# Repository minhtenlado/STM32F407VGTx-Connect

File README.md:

# STM32F407VGTx Connect — Wi-Fi & Bluetooth LE Development Board

**4-Layer PCB | KiCad 10 | STM32F407 + STM32F103 + ESP32-C3**

**Custom STM32 development board** based on the **STM32F407VGTx (ARM Cortex-M4)**, designed in **KiCad 10** with an **STM32F103CBTx onboard debug-probe circuit**, **USB Type-C**, **ESP32-C3 Wi-Fi/Bluetooth LE**, a **3.3 V / 3 A buck regulator**, and GPIO expansion headers.

> [!IMPORTANT]
> **Trạng thái dự án:** Repository chứa **schematic, PCB 4 lớp, hình ảnh 3D, Gerber/Drill, BOM, dữ liệu placement, thư viện AP63300WU-7 và mã nguồn firmware debug tham khảo**. Các file đã được thiết kế/xuất từ KiCad; **chưa có bằng chứng bo đã được lắp ráp và thử nghiệm thực tế**, cũng chưa có báo cáo ERC/DRC được xác minh kèm theo.
>
> **`firrmware_STLINKV2/` chứa mã nguồn [dap42](https://github.com/devanlai/dap42) (CMSIS-DAP nguồn mở), KHÔNG phải firmware ST-LINK/V2 chính hãng.** Không được mặc định rằng firmware tham khảo sẽ chạy ngay trên bo tự thiết kế nếu chưa kiểm tra chân MCU, USB và clock.

## 1. PCB 3D Preview

### Tổng quan bo mạch

### Hai góc nhìn 3D bổ sung

| 3D View 01 | 3D View 02|
| :---: | :---: |
|  |  |

> **Lưu ý:** Cả ba ảnh là bản dựng 3D từ KiCad, chưa phải ảnh bo mạch đã gia công hoặc lắp ráp. Nhấn vào từng ảnh để mở bản gốc.

## 2. PCB Layout — 4 Copper Layers

Bo mạch được thiết kế với **bốn lớp đồng**: `F.Cu`, `In1.Cu`, `In2.Cu`, `B.Cu`. Các hình dưới đây được lấy trực tiếp từ thư mục [`Images/`](Images/) trong project.

| Front Copper — `F.Cu` | Inner Copper 1 — `In1.Cu` |
| :---: | :---: |
|  |  |

| Inner Copper 2 — `In2.Cu` | Back Copper — `B.Cu` |
| :---: | :---: |
|  |  |

### Toàn bộ các lớp đồng

### Bố trí footprint

> [!NOTE]
> Ảnh các lớp và tập tin sản xuất là **kết quả xuất thiết kế**. Chúng chưa chứng minh các đường tín hiệu đã qua kiểm tra SI/EMC, ERC/DRC hoặc kiểm thử phần cứng.

## 3. System Architecture

```mermaid
flowchart TB
    HOST["PC / Laptop"] -->|"USB Type-C / J2"| USB["USB D+ / D- + Type-C CC"]
    USB --> F103["STM32F103CBTx / U1<br/>Onboard CMSIS-DAP candidate"]
    F103 -->|"SWDIO / SWCLK / NRST"| F407["STM32F407VGTx / U3<br/>Main MCU — Cortex-M4"]
    F103 <-->|"USART / Virtual COM planned"| F407
    F407 <-->|"UART2"| ESP["ESP32-C3-WROOM-02 / U4<br/>2.4 GHz Wi-Fi + Bluetooth LE"]
    F407 --- GPIO["GPIO expansion headers"]
    USB -->|"VBUS / D3"| PWR["AP63300WU-7 / U5<br/>3.3 V Buck regulator"]
    PWR --> F103
    PWR --> F407
    PWR --> ESP
    PROG["External SWD programmer"] -->|"J1 / program the STM32F103"| F103
    EXT["External UART programmer"] -->|"J13 / ESP32 UART0"| ESP
```

Đây là **kiến trúc phần cứng dự kiến**. Các chức năng CMSIS-DAP, Virtual COM và Wi-Fi/BLE chỉ hoạt động sau khi có firmware đúng và kiểm thử trên bo thực tế.

## 4. Hardware Overview

| Khối | Linh kiện / đầu nối thực tế | Vai trò |
| --- | --- | --- |
| Main MCU | **U3 — STM32F407VGTx** | MCU ARM Cortex-M4, chạy ứng dụng chính |
| Debug MCU | **U1 — STM32F103CBTx** | Phần cứng debug probe tích hợp, dự kiến dùng CMSIS-DAP |
| Wireless | **U4 — ESP32-C3-WROOM-02** | Wi-Fi 2.4 GHz, Bluetooth Low Energy (BLE) |
| USB | **J2 — USB-C 2.0 (16 chân)** | USB dữ liệu và cấp nguồn đầu vào |
| USB ESD | **U2 — USBLC6-2SC6** | Bảo vệ ESD cho USB D+/D− |
| Power converter | **U5 — AP63300WU-7**, **L1 — 4.7 µH** | Buck 5 V sang 3.3 V, IC có định mức đầu ra tới 3 A |
| Reverse-current blocking | **D3 — SS34** | Diode Schottky trên đường cấp nguồn USB |
| Clocks | **Y1, Y2 — 8 MHz** | HSE riêng cho STM32F103 và STM32F407 |
| GPIO expansion | **J3, J4, J5, J11, J12** | Các chân mở rộng thể hiện trong project |
| Debug-MCU programming | **J1 — 1×5 header** | Nạp/khôi phục STM32F103 bằng SWD ngoài |
| ESP32 programming | **J13 — 1×5 header** | Đầu nối UART0 của ESP32-C3 |
| UART jumpers | **JP1, JP2** | Cho phép ngắt/nối UART giữa STM32F407 và ESP32 |
| User controls | **S1, S2, S3, SW2** | Các nút nhấn và công tắc theo schematic |
| Custom library | **`library/AP63300WU-7/`** | Symbol, footprint và mô hình STEP của U5 |

### Nguồn hệ thống

Nguồn USB đi qua **D3 (SS34)**; **AP63300WU-7** tạo đường **3.3 V** cho các mạch trên bo. Thiết kế Buck có **L1 = 4.7 µH**, tụ bootstrap, cầu chia áp FB và các tụ lọc đầu vào/đầu ra.

> [!WARNING]
> **3 A là định mức đầu ra của IC Buck, không phải mức dòng mà mọi cổng USB-C máy tính cho phép lấy.** Dòng khả dụng phụ thuộc nguồn USB, điện trở CC, dây cáp, bảo vệ quá dòng và tải thực tế. Cần kiểm tra dòng đỉnh của ESP32-C3, nhiệt độ linh kiện và khả năng cấp nguồn trước khi khai thác toàn bộ tải.
>
> USBLC6-2SC6 bảo vệ **xung ESD**; nó **không thay thế** thiết bị giới hạn quá dòng liên tục trên VBUS.

### HSE và RTC

- **Y1 = 8 MHz:** nguồn HSE dự kiến cho STM32F103.
- **Y2 = 8 MHz:** HSE của STM32F407, nối với **PH0/OSC_IN** và **PH1/OSC_OUT**.
- Các tụ tải được thể hiện trong schematic; giá trị cuối cần đối chiếu datasheet của đúng mã thạch anh và ký sinh layout.
- Thiết kế không sử dụng thạch anh RTC/LSE ngoài 32.768 kHz.

## 5. STM32 Programming, Debugging & UART

### A. Onboard debug path

Đường debug được thiết kế như sau:

`PC → J2 USB-C → U1 STM32F103 → SWD → U3 STM32F407`

| Chức năng | STM32F103 (U1) | STM32F407 (U3) |
| --- | --- | --- |
| SWDIO | PB14 | PA13 |
| SWCLK | PB13 | PA14 |
| Target reset | PB0 | NRST |
| UART đến MCU chính | PA2 / USART2_TX | PD9 / USART3_RX |
| UART từ MCU chính | PA3 / USART2_RX | PD8 / USART3_TX |

**Chân U1, U3 và tên net cần được đối chiếu trong bản schematic đang phát hành** trước khi thay đổi firmware hoặc PCB. Các đường SWD/UART được thiết kế cho chức năng debug và Virtual COM, **không có nghĩa thiết bị đã được nhận là ST-LINK trên PC**.

### B. First-time programming of debug MCU

**J1 là header dùng để nạp chính U1 (STM32F103)** theo BOM của project. Khi STM32F103 mới chưa có firmware, cần **probe SWD bên ngoài** để nạp firmware probe lần đầu. Không nhầm J1 với cổng debug mặc định của STM32F407.

### C. ESP32-C3 UART

Sơ đồ dành hai đường UART giữa MCU chính và ESP32-C3, qua **JP1/JP2**:

| STM32F407 | ESP32-C3 | Hướng tín hiệu |
| --- | --- | --- |
| PD5 / USART2_TX | GPIO6 (RX do firmware cấu hình) | STM32 → ESP32 |
| PD6 / USART2_RX | GPIO7 (TX do firmware cấu hình) | ESP32 → STM32 |

Đóng JP1/JP2 để nối UART. Trên ESP32-C3, UART có thể gán qua GPIO Matrix; firmware phải cấu hình đúng chân, điện áp logic **3.3 V**, tốc độ baud và giao thức.

## 6. Debugger Firmware — dap42 / CMSIS-DAP

Mã nguồn đi kèm được lưu tại [`firrmware_STLINKV2/`](firrmware_STLINKV2/). **Tên thư mục được giữ đúng như trong project, kể cả cách viết `firrmware`.**

> [!IMPORTANT]
> Đây là mã nguồn **[dap42](https://github.com/devanlai/dap42)** cho CMSIS-DAP, **không phải firmware ST-LINK/V2 chính thức**. Dự án dap42 có nhiều cấu hình STM32F103 cho các bo khác nhau. Cần sửa/đối chiếu chân debug, USB RENUM, LED, HSE và UART với phần cứng của project này trước khi sử dụng.

### Nội dung firmware hiện có

| Đường dẫn | Nội dung |
| --- | --- |
| [`firrmware_STLINKV2/src/`](firrmware_STLINKV2/src/) | Mã nguồn CMSIS-DAP, USB và cấu hình MCU |
| [`firrmware_STLINKV2/src/targets.mk`](firrmware_STLINKV2/src/targets.mk) | Danh sách build target |
| [`firrmware_STLINKV2/Makefile`](firrmware_STLINKV2/Makefile) | Hệ thống build |
| [`firrmware_STLINKV2/openocd/`](firrmware_STLINKV2/openocd/) | Ví dụ cấu hình OpenOCD |
| [`firrmware_STLINKV2/FLASHING.md`](firrmware_STLINKV2/FLASHING.md) | Hướng dẫn nạp firmware từ upstream |
| [`firrmware_STLINKV2/LICENSE`](firrmware_STLINKV2/LICENSE) | Giấy phép nguồn firmware |

### Biên dịch firmware tham khảo (Ubuntu)

Bản RAR **chưa có mã nguồn trong `firrmware_STLINKV2/libopencm3/`**; cần bổ sung dependency trước khi build.

```bash
sudo apt update
sudo apt install git make gcc-arm-none-eabi binutils-arm-none-eabi

cd firrmware_STLINKV2
# Chỉ thực hiện nếu thư mục libopencm3 đang trống
 git clone https://github.com/libopencm3/libopencm3.git libopencm3

# Ví dụ build cho profile STM32F103 Blue Pill của dap42:
make DAP103-BLUEPILL.bin
```

> [!CAUTION]
> **Không nạp thẳng file `DAP103-BLUEPILL.bin` lên U1 của PCB này** trước khi đối chiếu `src/stm32f103/bluepill/target.c`, `config.h`, mạch điều khiển USB pull-up `RENUM` và UART. Đây mới là ví dụ về **cách build target có sẵn**, không phải firmware đã tùy biến và kiểm chứng cho bo STM32F407 Wi-Fi/BLE.

Tham khảo thêm: [dap42 upstream](https://github.com/devanlai/dap42) · [libopencm3](https://github.com/libopencm3/libopencm3) · [OpenOCD](https://openocd.org/).

## 7. ESP32-C3 Wi-Fi & Bluetooth LE

**ESP32-C3-WROOM-02 (U4)** cung cấp kết nối **Wi-Fi 2.4 GHz và Bluetooth Low Energy**. ESP32-C3 **không hỗ trợ Bluetooth Classic**.

- **J13 (`ESP32_UART0_PROG`)**: chân UART0 phục vụ nạp và kiểm tra module.
- **JP1/JP2**: cầu nối UART với STM32F407.
- Dữ liệu qua Wi-Fi/BLE cần firmware riêng cho ESP32-C3; **project RAR hiện không chứa firmware ứng dụng hoàn chỉnh cho U3 hoặc U4**.
- Khi bố trí anten ESP32-C3 phải tuân thủ vùng keep-out, không đổ đồng hoặc đặt kim loại vào khu vực cấm theo tài liệu module.

## 8. Project Structure

```text
STM32F407VGTx_wifi/
├── README.md
├── STM32F407VGTx_wifi.kicad_pro      # KiCad project
├── STM32F407VGTx_wifi.kicad_sch      # Full schematic
├── STM32F407VGTx_wifi.kicad_pcb      # 4-layer PCB
├── schematic.pdf                     # PDF schematic
├── Images/
│   ├── board_3D(1).png              # 3D top view
│   ├── board_3D(2).png              # 3D isometric view
│   ├── board_3D(3).png              # 3D supplementary view
│   ├── F_cu.png                     # Front copper
│   ├── in1.png                      # Inner copper layer 1
│   ├── in2.png                      # Inner copper layer 2
│   ├── B_cu.png                     # Back copper
│   ├── ALL_layers.png               # All layers overview
│   └── footprint.png                # Component placement
├── production/
│   ├── STM32F407VGTx_wifi.zip       # Gerber + drill files (4 layers)
│   ├── bom.csv                      # Bill of materials
│   ├── positions.csv                # Component positions
│   ├── designators.csv              # Designator list
│   └── netlist.ipc                  # IPC netlist
├── library/
│   └── AP63300WU-7/                 # Custom symbol, footprint and STEP
│       ├── AP63300WU-7.kicad_sym
│       ├── SOT95P280X100-6N.kicad_mod
│       └── AP63300WU-7.step
└── firrmware_STLINKV2/              # Upstream dap42 CMSIS-DAP source
    ├── src/
    ├── openocd/
    ├── drivers/
    ├── Makefile
    ├── FLASHING.md
    ├── LICENSE
    └── README.md
```

> `Images/` dùng **chữ I viết hoa**; tên `in1.png` và `in2.png` cũng viết thường như trong RAR. GitHub phân biệt chữ hoa/chữ thường trong đường dẫn.

### Quick Links

| Tài nguyên | Liên kết |
| --- | --- |
| KiCad PCB | [STM32F407VGTx_wifi.kicad_pcb](STM32F407VGTx_wifi.kicad_pcb) |
| KiCad schematic | [STM32F407VGTx_wifi.kicad_sch](STM32F407VGTx_wifi.kicad_sch) |
| Schematic PDF | [schematic.pdf](schematic.pdf) |
| Gerber + Drill ZIP | [production/STM32F407VGTx_wifi.zip](production/STM32F407VGTx_wifi.zip) |
| BOM | [production/bom.csv](production/bom.csv) |
| Placement | [production/positions.csv](production/positions.csv) |
| Full images | [Images/](Images/) |
| CMSIS-DAP firmware source | [firrmware_STLINKV2/](firrmware_STLINKV2/) |
| AP63300WU-7 library | [library/AP63300WU-7/](library/AP63300WU-7/) |

### Mở project trên KiCad 10

1. Tải/clone repository rồi giữ nguyên cấu trúc thư mục.
2. Mở file `STM32F407VGTx_wifi.kicad_pro` bằng **KiCad 10**.
3. Kiểm tra và khai báo thư viện tùy chỉnh **AP63300WU-7** nếu KiCad báo không tìm thấy symbol/footprint.
4. Mở Schematic Editor → **Inspect → Electrical Rules Checker (ERC)**.
5. Mở PCB Editor → **Inspect → Design Rules Checker (DRC)**, kiểm tra lại netlist và quy tắc sản xuất trước khi xuất Gerber mới.

## 9. Verification Checklist

- [x] Có project KiCad 10 và schematic đầy đủ.
- [x] Có PCB **4 lớp đồng** `F.Cu`, `In1.Cu`, `In2.Cu`, `B.Cu`.
- [x] Có ba ảnh 3D, bốn ảnh lớp đồng, ảnh tổng hợp và footprint.
- [x] Có tập tin Gerber, drill, BOM, component positions và IPC netlist.
- [x] Có thiết kế STM32F407VGTx, STM32F103CBTx, ESP32-C3 và nguồn AP63300WU-7.
- [x] Có IC USBLC6-2SC6 bảo vệ ESD ở đường USB.
- [x] Có mã nguồn dap42/CMSIS-DAP để tham khảo tích hợp debug.
- [ ] Chạy và lưu **báo cáo ERC/DRC** với số lỗi đã xử lý.
- [ ] Xác nhận footprint, pin số, 3D model, vị trí pad và BOM trùng linh kiện đặt mua.
- [ ] Kiểm tra USB Type-C/CC, `RENUM`, bảo vệ VBUS và dòng cấp nguồn từ USB thực tế.
- [ ] Xác nhận HSE 8 MHz, VCAP, boot/reset, SWD và UART trên nguyên mẫu.
- [ ] Hoàn thiện bản firmware CMSIS-DAP tương thích chân U1 và kiểm tra nạp/debug U3.
- [ ] Hoàn thiện firmware STM32F407 và ESP32-C3, thử Wi-Fi/BLE thực tế.
- [ ] Thử nghiệm PCB đã lắp ráp, kiểm tra nhiệt, ổn định nguồn và mức nhiễu.

## 10. Safety & Licensing

- Các chân MCU, SWD, UART và ESP32-C3 dùng mức logic **3.3 V**, không tùy tiện cấp tín hiệu 5 V vào chân không chịu được 5 V.
- Tải dòng lớn qua USB cần có giới hạn dòng phù hợp; **định mức Buck 3 A không bảo đảm nguồn USB cấp được 3 A**.
- Các file sản xuất là **tài liệu thiết kế** và chưa thay thế cho báo cáo kiểm định phần cứng.
- **Phần cứng:** Repository chưa có `LICENSE` riêng xác nhận việc cấp phép lại schematic, PCB hoặc ảnh thiết kế. Việc công khai trên GitHub không tự động tương đương open-source hardware.
- **Firmware:** Mã nguồn dap42 là dự án bên thứ ba; giữ nguyên các giấy phép và thông báo bản quyền trong [`firrmware_STLINKV2/LICENSE`](firrmware_STLINKV2/LICENSE) và các thành phần liên quan.

---

**Designed by Phan Huynh Van Do** · **Hardware Rev 1.0** · **2026**

*STM32F407 Wi-Fi & Bluetooth Development Board — integrated debug, wireless connectivity and flexible embedded development.*

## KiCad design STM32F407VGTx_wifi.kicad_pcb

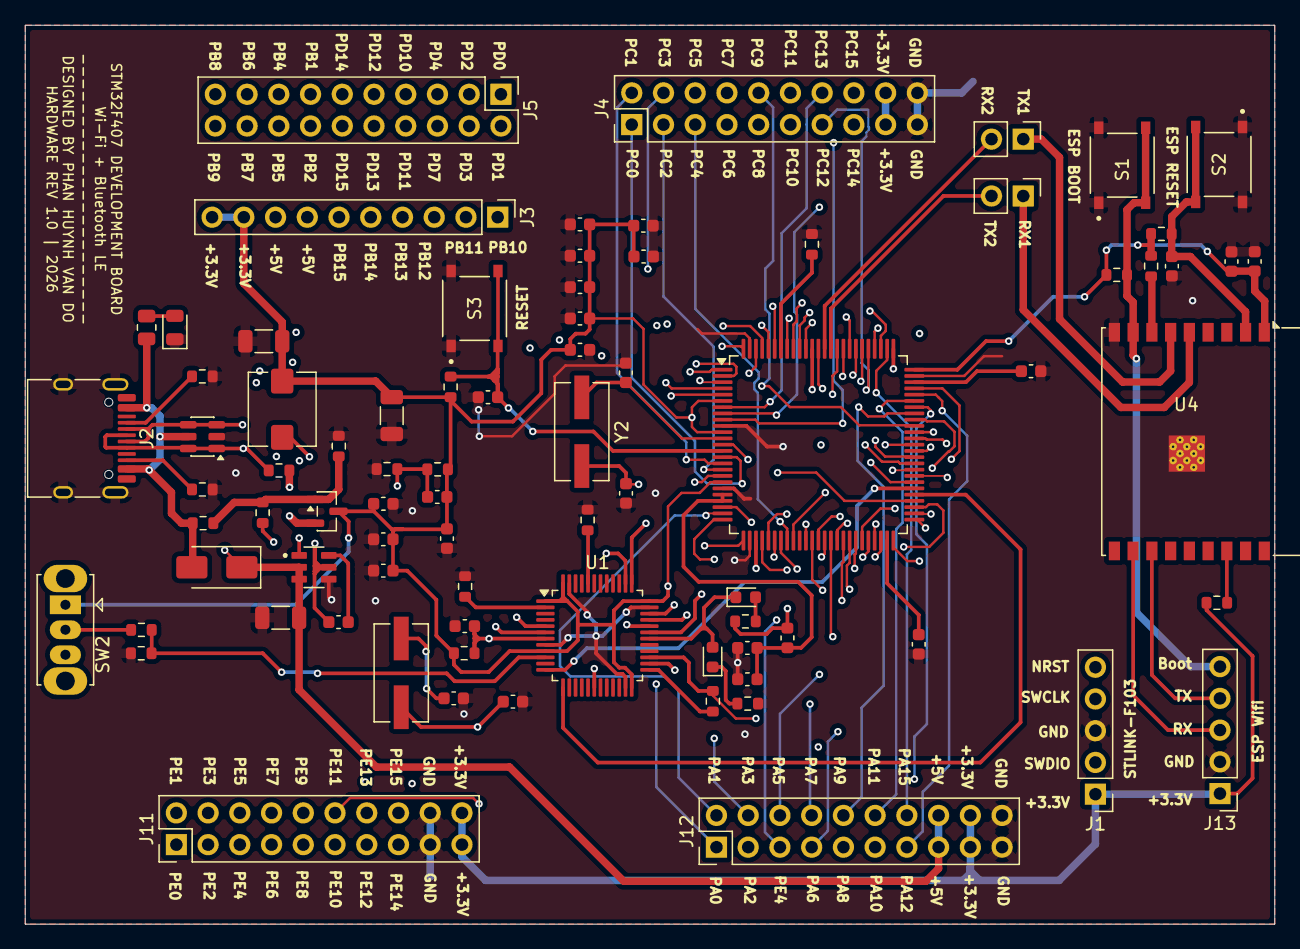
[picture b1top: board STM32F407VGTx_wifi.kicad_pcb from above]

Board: 4 copper layers, 100.0 x 71.9 mm, 81 parts (1 on the bottom side), 122 nets.

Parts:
C1, C4, C5, C6, C7, C12, C14, C15, C16, C17, C18, C19, C20, C21, C22, C25: 100nF; C_0603_1608Metric
C2, C3, C27, C28: 20pF; C_0603_1608Metric
C8: 10uF; C_1206_3216Metric
C9, C24: 22uF; C_1206_3216Metric
C10, C11: 2.2uF; C_0603_1608Metric
C13, C62: 1uF; C_0603_1608Metric
C23: 10uF; C_0603_1608Metric
C26: 56pF; C_0603_1608Metric
D1: RED; LED_0603_1608Metric
D2: BLUE; LED_0603_1608Metric
D3: SS34; D_SMA
D13: LED Red; LED_0805_2012Metric
FB1: FerriteBead; L_0603_1608Metric
J1: Dùng nạp cho U1; PinHeader_1x05_P2.54mm_Vertical
J2: USB_C_Receptacle_USB2.0_16P; USB_C_Receptacle_HRO_TYPE-C-31-M-12
J3: Conn_01x10_Pin; PinHeader_1x10_P2.54mm_Vertical
J4, J5: GPIO_B_C_D; PinHeader_2x10_P2.54mm_Vertical
J11: GPIO_D_E; PinHeader_2x10_P2.54mm_Vertical
J12: GPIO_A_B; PinHeader_2x10_P2.54mm_Vertical
J13: ESP32_UART0_PROG; PinHeader_1x05_P2.54mm_Vertical
JP1, JP2: Jumper_2_Open; PinHeader_1x02_P2.54mm_Vertical
L1: 4.7uH; L_Bourns_SRP5030T
Q1: BC849; SOT-23
R1, R2: 100k; R_0603_1608Metric
R3, R11, R14, R15, R18, R19, R20, R21: 10K; R_0603_1608Metric
R5, R7: 4K7; R_0603_1608Metric
R6, R10: 100R; R_0603_1608Metric
R8: 200R; R_0603_1608Metric
R9: 220R; R_0603_1608Metric
R12: 39K; R_0603_1608Metric
R13: 1K5; R_0603_1608Metric
R16, R17: 5.1K; R_0603_1608Metric
R22: 93.1K; R_0603_1608Metric
R23: 30.1K; R_0603_1608Metric
R58: 1K; R_0805_2012Metric
S1, S2, S3: TS-1187A-B-A-B; SW_TS-1187A-B-A-B
SW2: F103_USER_SW_3V3_GND; SW_Slide_SPDT_Straight_CK_OS102011MS2Q
U1: STM32F103CBTx; LQFP-48_7x7mm_P0.5mm
U2: USBLC6-2SC6; SOT-23-6
U3: STM32F407VGTx; LQFP-100_14x14mm_P0.5mm
U4: ESP32-C3-WROOM-02
U5: AP63300WU-7; SOT95P280X100-6N
WE: https://phanhuynh.id.vn/; //phanhuynh.id.vn/
Y1, Y2: 8MHz; Crystal_SMD_ECS_CSM3X-2Pin_7.6x4.1mm

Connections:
/+3V3_STLINK: C4.2, C5.2, C6.2, C7.2, C9.2, C15.2, C16.2, C17.2, C18.2, C19.2, C20.2, C21.2, C22.1, C23.1, C24.2, C26.2, FB1.1, J1.1, J3.9, J3.10, J4.17, J4.18, J11.19, J11.20, J12.17, J12.18, J13.1, L1.2, Q1.3 (C), R1.2, R8.1, R15.2, R18.1, R19.1, R20.2, R21.2, R22.1, SW2.1 (A), U1.1 (VBAT), U1.9 (VDDA), U1.24 (VDD), U1.36 (VDD), U1.48 (VDD), U3.6 (VBAT), U3.11 (VDD), U3.19 (VDD), U3.28 (VDD), U3.50 (VDD), U3.75 (VDD), U3.100 (VDD), U4.1 (3V3)
/+5V_STLINK_IN: C8.2, D3.1 (K), J3.7, J3.8, J12.15, J12.16, U5.2 (EN), U5.3 (VIN)
/B0: R2.1, U1.44 (BOOT0)
/D +: J2.A6 (D+), J2.B6 (D+), R13.1, U1.33 (PA12), U2.1 (I/O1), U2.6 (I/O1)
/D -: J2.A7 (D-), J2.B7 (D-), U1.32 (PA11), U2.3 (I/O2), U2.4 (I/O2)
/ESP_BOOT: J13.5, R19.2, S1.C, S1.D, U4.8 (IO9)
/ESP_UART0_RX: J13.3, U4.11 (IO20/RXD)
/ESP_UART0_TX: J13.4, U4.12 (IO21/TXD)
/ESP_UART1_RX: JP1.1 (A), U4.5 (IO6)
/ESP_UART1_TX: JP2.1 (A), U4.6 (IO7)
/EXT_PA0: J12.1, U3.23 (PA0)
/EXT_PA1: J12.2, U3.24 (PA1)
/EXT_PA2: J12.3, U3.25 (PA2)
/EXT_PA3: J12.4, U3.26 (PA3)
/EXT_PA4: J12.5, U3.29 (PA4)
/EXT_PA5: J12.6, U3.30 (PA5)
/EXT_PA6: J12.7, U3.31 (PA6)
/EXT_PA7: J12.8, U3.32 (PA7)
/EXT_PA8: J12.9, U3.67 (PA8)
/EXT_PA9: J12.10, U3.68 (PA9)
/EXT_PA10: J12.11, U3.69 (PA10)
/EXT_PA11: J12.12, U3.70 (PA11)
/EXT_PA12: J12.13, U3.71 (PA12)
/EXT_PA15: J12.14, U3.77 (PA15)
/EXT_PB1: J5.13, U3.36 (PB1)
/EXT_PB2: J5.14, U3.37 (PB2)
/EXT_PB4: J5.15, U3.90 (PB4)
/EXT_PB5: J5.16, U3.91 (PB5)
/EXT_PB6: J5.17, U3.92 (PB6)
/EXT_PB7: J5.18, U3.93 (PB7)
/EXT_PB8: J5.19, U3.95 (PB8)
/EXT_PB9: J5.20, U3.96 (PB9)
/EXT_PB10: J3.1, U3.47 (PB10)
/EXT_PB11: J3.2, U3.48 (PB11)
/EXT_PB12: J3.3, U3.51 (PB12)
/EXT_PB13: J3.4, U3.52 (PB13)
/EXT_PB14: J3.5, U3.53 (PB14)
/EXT_PB15: J3.6, U3.54 (PB15)
/EXT_PC0: J4.1, U3.15 (PC0)
/EXT_PC1: J4.2, U3.16 (PC1)
/EXT_PC2: J4.3, U3.17 (PC2)
/EXT_PC3: J4.4, U3.18 (PC3)
/EXT_PC4: J4.5, U3.33 (PC4)
/EXT_PC5: J4.6, U3.34 (PC5)
/EXT_PC6: J4.7, U3.63 (PC6)
/EXT_PC7: J4.8, U3.64 (PC7)
/EXT_PC8: J4.9, U3.65 (PC8)
/EXT_PC9: J4.10, U3.66 (PC9)
/EXT_PC10: J4.11, U3.78 (PC10)
/EXT_PC11: J4.12, U3.79 (PC11)
/EXT_PC12: J4.13, U3.80 (PC12)
/EXT_PC13: J4.14, U3.7 (PC13)
/EXT_PC14: J4.15, U3.8 (PC14)
/EXT_PC15: J4.16, U3.9 (PC15)
/EXT_PD0: J5.1, U3.81 (PD0)
/EXT_PD1: J5.2, U3.82 (PD1)
/EXT_PD2: J5.3, U3.83 (PD2)
/EXT_PD3: J5.4, U3.84 (PD3)
/EXT_PD4: J5.5, U3.85 (PD4)
/EXT_PD7: J5.6, U3.88 (PD7)
/EXT_PD10: J5.7, U3.57 (PD10)
/EXT_PD11: J5.8, U3.58 (PD11)
/EXT_PD12: J5.9, U3.59 (PD12)
/EXT_PD13: J5.10, U3.60 (PD13)
/EXT_PD14: J5.11, U3.61 (PD14)
/EXT_PD15: J5.12, U3.62 (PD15)
/EXT_PE0: J11.1, U3.97 (PE0)
/EXT_PE1: J11.2, U3.98 (PE1)
/EXT_PE2: J11.3, U3.1 (PE2)
/EXT_PE3: J11.4, U3.2 (PE3)
/EXT_PE4: J11.5, U3.3 (PE4)
/EXT_PE5: J11.6, U3.4 (PE5)
/EXT_PE6: J11.7, U3.5 (PE6)
/EXT_PE7: J11.8, U3.38 (PE7)
/EXT_PE8: J11.9, U3.39 (PE8)
/EXT_PE9: J11.10, U3.40 (PE9)
/EXT_PE10: J11.11, U3.41 (PE10)
/EXT_PE11: J11.12, U3.42 (PE11)
/EXT_PE12: J11.13, U3.43 (PE12)
/EXT_PE13: J11.14, U3.44 (PE13)
/EXT_PE14: J11.15, U3.45 (PE14)
/EXT_PE15: J11.16, U3.46 (PE15)
/F103_NRST: C1.1, J1.5, R1.1, U1.7 (NRST)
/F103_SWCLK: J1.4, U1.37 (PA14)
/F103_SWDIO: J1.2, U1.34 (PA13)
/F407_TX_PROBE_RX: U1.13 (PA3), U3.55 (PD8)
/F407_UART2_RX: JP2.2 (B), U3.87 (PD6)
/F407_UART2_TX: JP1.2 (B), U3.86 (PD5)
/LED: D1.2 (A), D2.1 (K), U1.30 (PA9)
/PH0: C27.1, U3.12 (PH0), Y2.1
/PH1: C28.1, U3.13 (PH1), Y2.2
/PROBE_TX_F407_RX: U1.12 (PA2), U3.56 (PD9)
/RENUM: R10.2, U1.38 (PA15)
/T_CLK: U1.26 (PB13), U3.76 (PA14)
/T_DIO: R6.1, U1.27 (PB14), U3.72 (PA13)
/T_RST: C12.1, R15.1, S3.C, S3.D, U1.18 (PB0), U3.14 (NRST)
/T_SWO: U1.31 (PA10), U3.89 (PB3)
/VDDA: C13.1, C14.1, FB1.2, U3.21 (VREF+), U3.22 (VDDA)
GND: C1.2, C2.2, C3.2, C4.1, C5.1, C6.1, C7.1, C8.1, C9.1, C10.2, C11.2, C12.2, C13.2, C14.2, C15.1, C16.1, C17.1, C18.1, C19.1, C20.1, C21.1, C22.2, C23.2, C24.1, C27.2, C28.2, C62.1, D13.1 (K), J1.3, J2.A1 (GND), J2.A12 (GND), J2.B1 (GND), J2.B12 (GND), J2.SH (SHIELD), J4.19, J4.20, J11.17, J11.18, J12.19, J12.20, J13.2, R2.2, R3.2, R5.2, R9.2, R12.1, R14.1, R16.1, R17.1, R23.1, S1.A, S1.B, S2.A, S2.B, S3.A, S3.B, U1.8 (VSSA), U1.23 (VSS), U1.35 (VSS), U1.47 (VSS), U2.2 (GND), U3.10 (VSS), U3.20 (VSSA), U3.27 (VSS), U3.74 (VSS), U3.99 (VSS), U4.9 (GND), U4.19 (GND), U5.4 (GND)
unnamed: D1.1 (K), R9.1
unnamed: D2.2 (A), R8.2
unnamed: D13.2 (A), R58.2
unnamed: J2.A5 (CC1), R17.2
unnamed: J2.B5 (CC2), R16.2
unnamed: Q1.1 (B), R10.1, R11.1, R12.2
unnamed: Q1.2 (E), R13.2
unnamed: R7.1, SW2.2 (B)
unnamed: R5.1, R7.2, U1.10 (PA0)
unnamed: R6.2, U1.25 (PB12)
unnamed: R3.1, U1.2 (PC13)
unnamed: C2.1, U1.5 (PD0), Y1.1
unnamed: C3.1, U1.6 (PD1), Y1.2
unnamed: R14.2, U3.94 (BOOT0)
unnamed: C11.1, U3.49 (VCAP_1)
unnamed: C10.1, U3.73 (VCAP_2)
unnamed: C62.2, R18.2, S2.C, S2.D, U4.2 (EN)
unnamed: R21.1, U4.16 (IO2)
unnamed: R20.1, U4.7 (IO8)
unnamed: C25.2, U5.6 (BST)
unnamed: C26.1, R22.2, R23.2, U5.1 (FB)
unnamed: C25.1, L1.1, U5.5 (SW)
VBUS: D3.2 (A), J2.A4 (VBUS), J2.A9 (VBUS), J2.B4 (VBUS), J2.B9 (VBUS), R11.2, R58.1, U2.5 (VBUS)

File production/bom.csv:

Designator,Footprint,Quantity,Value,LCSC Part #
"C1, C12, C14, C15, C16, C17, C18, C19, C20, C21, C22, C25, C4, C5, C6, C7",0603,16,100nF,
"C10, C11",0603,2,2.2uF,
"C13, C62",0603,2,1uF,
"C2, C27, C28, C3",0603,4,20pF,
C23,0603,1,10uF,
"C24, C9",1206,2,22uF,
C26,0603,1,56pF,
C8,1206,1,10uF,
D1,0603,1,RED,
D13,0805,1,LED Red,
D2,0603,1,BLUE,
D3,D_SMA,1,SS34,
FB1,0603,1,FerriteBead,
J1,PinHeader_1x05_P2.54mm_Vertical,1,Dùng nạp cho U1,
J11,PinHeader_2x10_P2.54mm_Vertical,1,GPIO_D_E,
J12,PinHeader_2x10_P2.54mm_Vertical,1,GPIO_A_B,
J13,PinHeader_1x05_P2.54mm_Vertical,1,ESP32_UART0_PROG,
J2,USB_C_Receptacle_HRO_TYPE-C-31-M-12,1,USB_C_Receptacle_USB2.0_16P,
J3,PinHeader_1x10_P2.54mm_Vertical,1,Conn_01x10_Pin,
"J4, J5",PinHeader_2x10_P2.54mm_Vertical,2,GPIO_B_C_D,
"JP1, JP2",PinHeader_1x02_P2.54mm_Vertical,2,Jumper_2_Open,
L1,L_Bourns_SRP5030T,1,4.7uH,
Q1,SOT-23,1,BC849,
"R1, R2",0603,2,100k,
"R10, R6",0603,2,100R,
"R11, R14, R15, R18, R19, R20, R21, R3",0603,8,10K,
R12,0603,1,39K,
R13,0603,1,1K5,
"R16, R17",0603,2,5.1K,
R22,0603,1,93.1K,
R23,0603,1,30.1K,
"R5, R7",0603,2,4K7,
R58,0805,1,1K,
R8,0603,1,200R,
R9,0603,1,220R,
"S1, S2, S3",SW_TS-1187A-B-A-B,3,TS-1187A-B-A-B,
SW2,SW_Slide_SPDT_Straight_CK_OS102011MS2Q,1,F103_USER_SW_3V3_GND,
U1,LQFP-48_7x7mm_P0.5mm,1,STM32F103CBTx,
U2,SOT-23-6,1,USBLC6-2SC6,
U3,LQFP-100_14x14mm_P0.5mm,1,STM32F407VGTx,
U4,ESP32-C3-WROOM-02,1,ESP32-C3-WROOM-02,
U5,SOT95P280X100-6N,1,AP63300WU-7,
WE,//phanhuynh.id.vn/,1,https://phanhuynh.id.vn/,
"Y1, Y2",Crystal_SMD_ECS_CSM3X-2Pin_7.6x4.1mm,2,8MHz,
